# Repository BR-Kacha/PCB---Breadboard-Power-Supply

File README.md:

# PCB---Breadboard-Power-Supply

In this project, I have developed the schemetic and designed the 2 layer PCB of the Power Supply board for the Breadboard circuit, which can give provide you 3.3V and 5V options in voltage. 
It is designed in KiCAD 8.
Right now I am adding option for 12V also. 

--UNDER DEVELOPMENT--

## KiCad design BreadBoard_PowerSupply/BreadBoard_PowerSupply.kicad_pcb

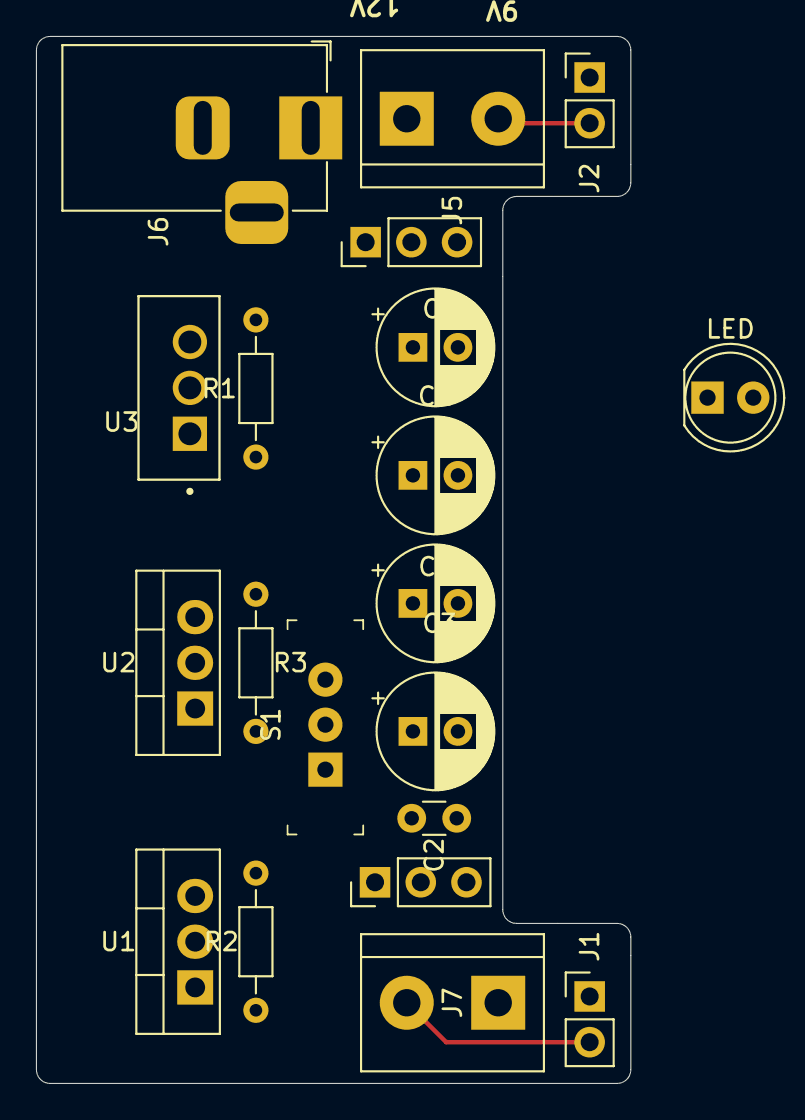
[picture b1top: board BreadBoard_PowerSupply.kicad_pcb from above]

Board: 2 copper layers, 33.0 x 58.2 mm, 20 parts (0 on the bottom side), 10 nets.

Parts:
C1: 10u; CP_Radial_D6.3mm_P2.50mm
C2: 0.1u; C_Disc_D3.0mm_W1.6mm_P2.50mm
C3: 1u; CP_Radial_D6.3mm_P2.50mm
C4: 220u; CP_Radial_D6.3mm_P2.50mm
C5: 47u; CP_Radial_D6.3mm_P2.50mm
D1: LED; LED_D5.0mm
J1, J2: Conn_01x02_Pin; PinHeader_1x02_P2.54mm_Vertical
J3, J4: Conn_01x03_Pin; PinHeader_1x03_P2.54mm_Vertical
J5, J7: Screw_Terminal_01x02; TerminalBlock_bornier-2_P5.08mm
J6: Barrel_Jack_Switch; BarrelJack_Horizontal
R1, R2: 330; R_Axial_DIN0204_L3.6mm_D1.6mm_P7.62mm_Horizontal
R3: 560; R_Axial_DIN0204_L3.6mm_D1.6mm_P7.62mm_Horizontal
S1: EG1218; Switch_Slide_11.6x4mm_EG1218
U1: LM7805_TO220; TO-220-3_Vertical
U2: LM317_TO-220; TO-220-3_Vertical
U3: L7809; TO255P1020X450X1968-3B

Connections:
/3.3V: C3.1, J3.1, R2.2, U2.2 (VO)
/5V: C2.1, J3.3, U1.3 (VO)
/9V: C5.1, J4.3, U3.3 (OUT)
/12V: C1.1, C4.1, J4.1, R1.2, S1.1, U1.1 (VI), U2.3 (VI), U3.1 (IN)
/PWR_INPUT: J6.1, S1.2
/PWR_OUTPUT_1: J2.2, J4.2, J5.2
/PWR_OUTPUT_2: J1.2, J3.2, J7.2
GND: C1.2, C2.2, C3.2, C4.2, C5.2, D1.1 (K), J1.1, J2.1, J5.1, J6.2, J6.3, J7.1, R3.1, U1.2 (GND), U3.2 (GND)
unnamed: D1.2 (A), R1.1
unnamed: R2.1, R3.2, U2.1 (ADJ)

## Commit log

2024-09-07 Updated
    12V and 9V circuit added to schematics, components arranged on PCB,
    Just have to confirm the sizes of components with available components in inventory and make the connections
